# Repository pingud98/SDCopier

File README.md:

# SDCopier
A cheap and simple board to copy SD cards

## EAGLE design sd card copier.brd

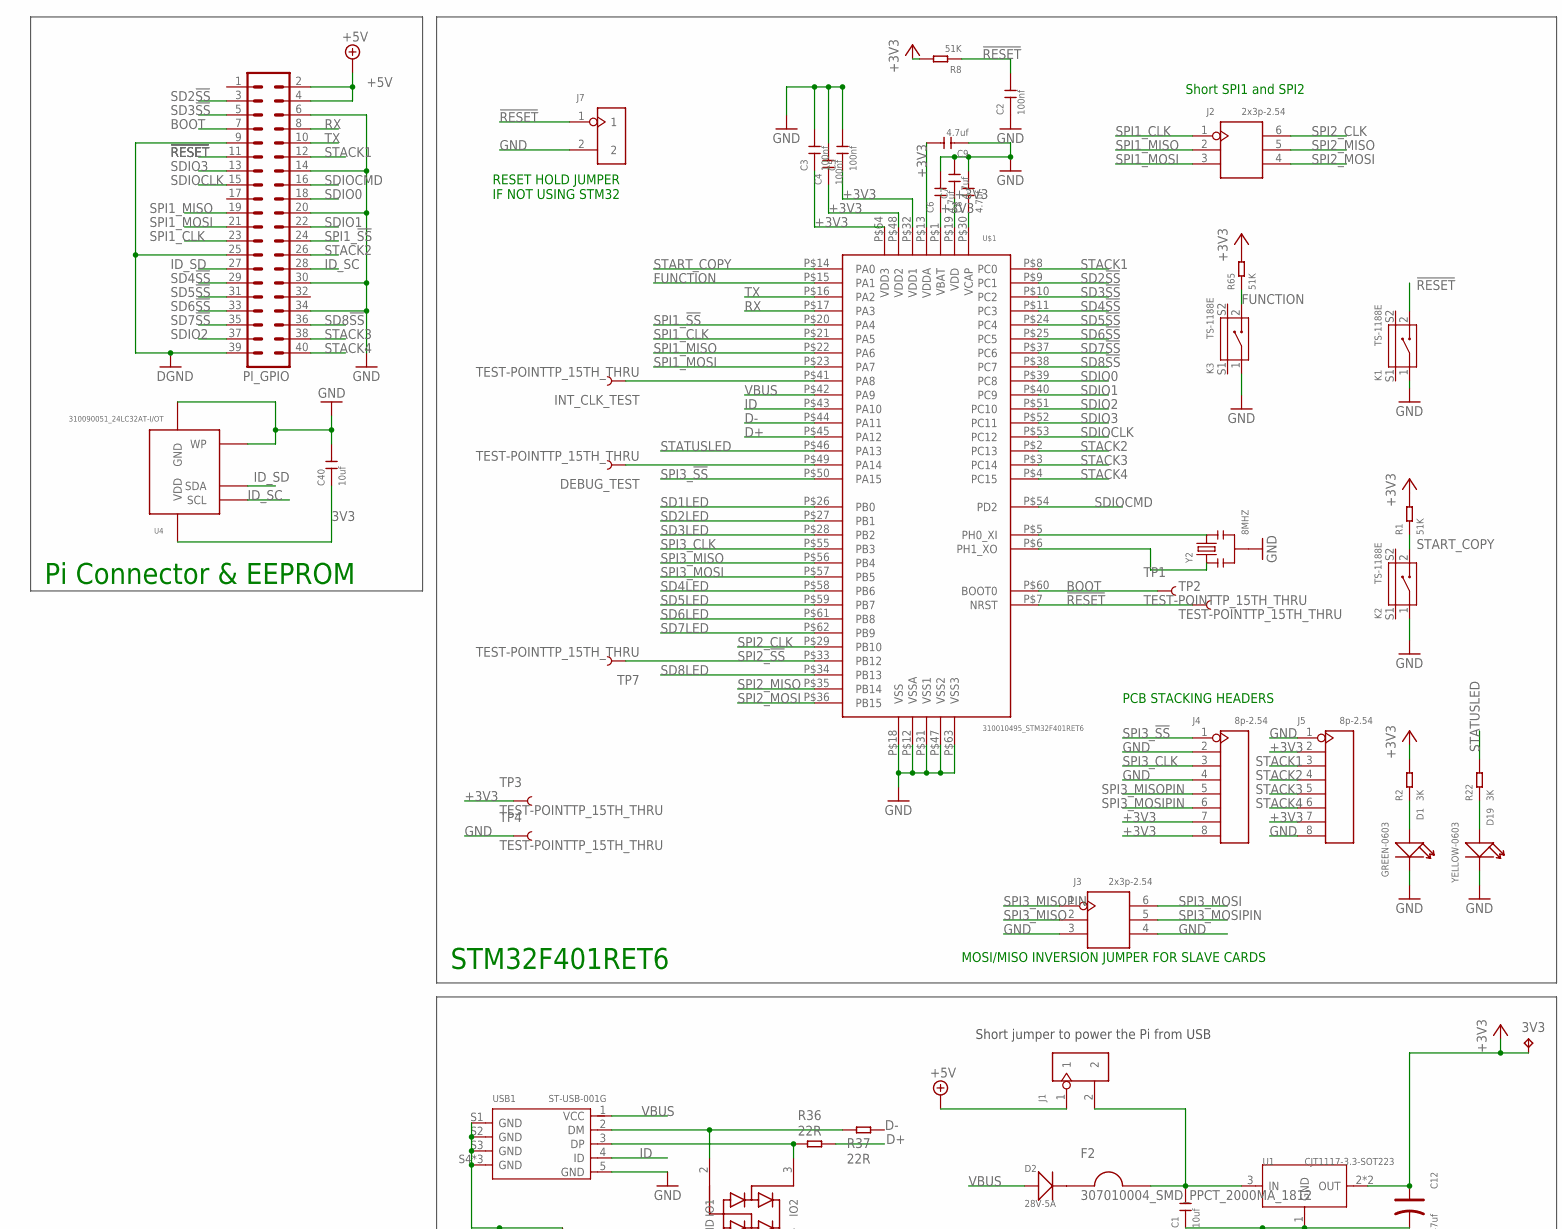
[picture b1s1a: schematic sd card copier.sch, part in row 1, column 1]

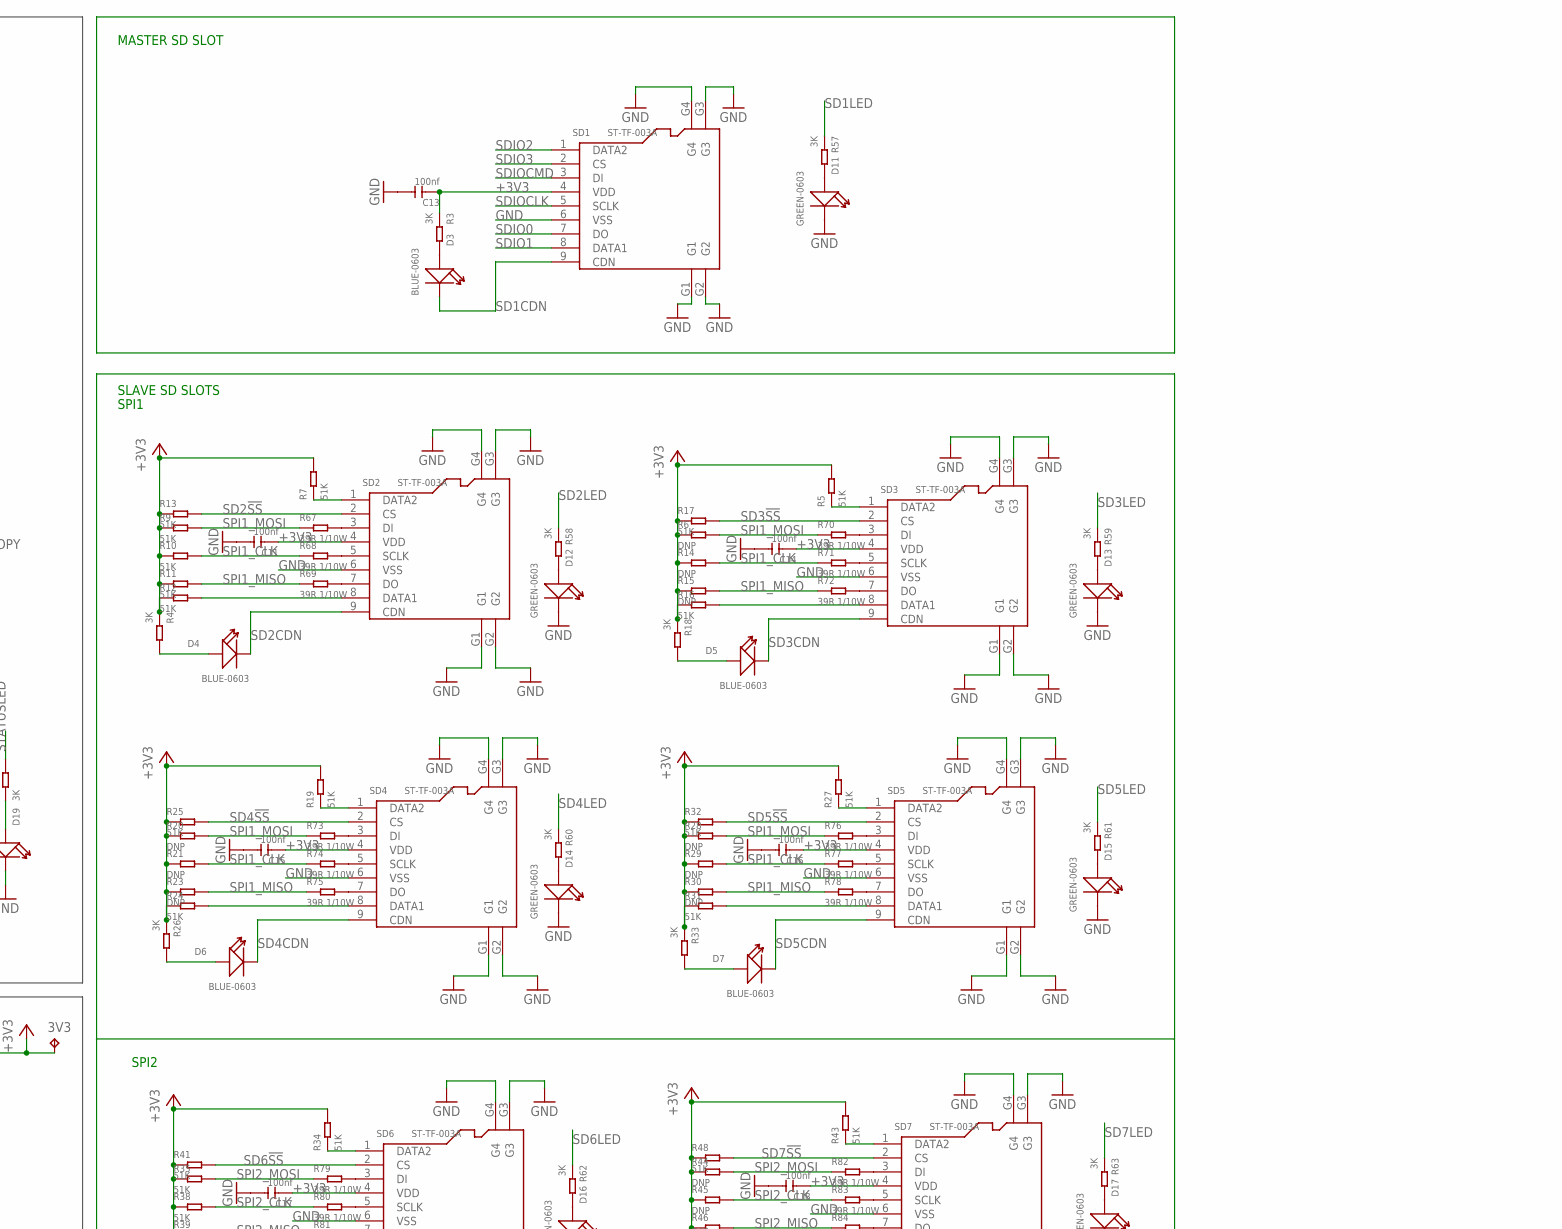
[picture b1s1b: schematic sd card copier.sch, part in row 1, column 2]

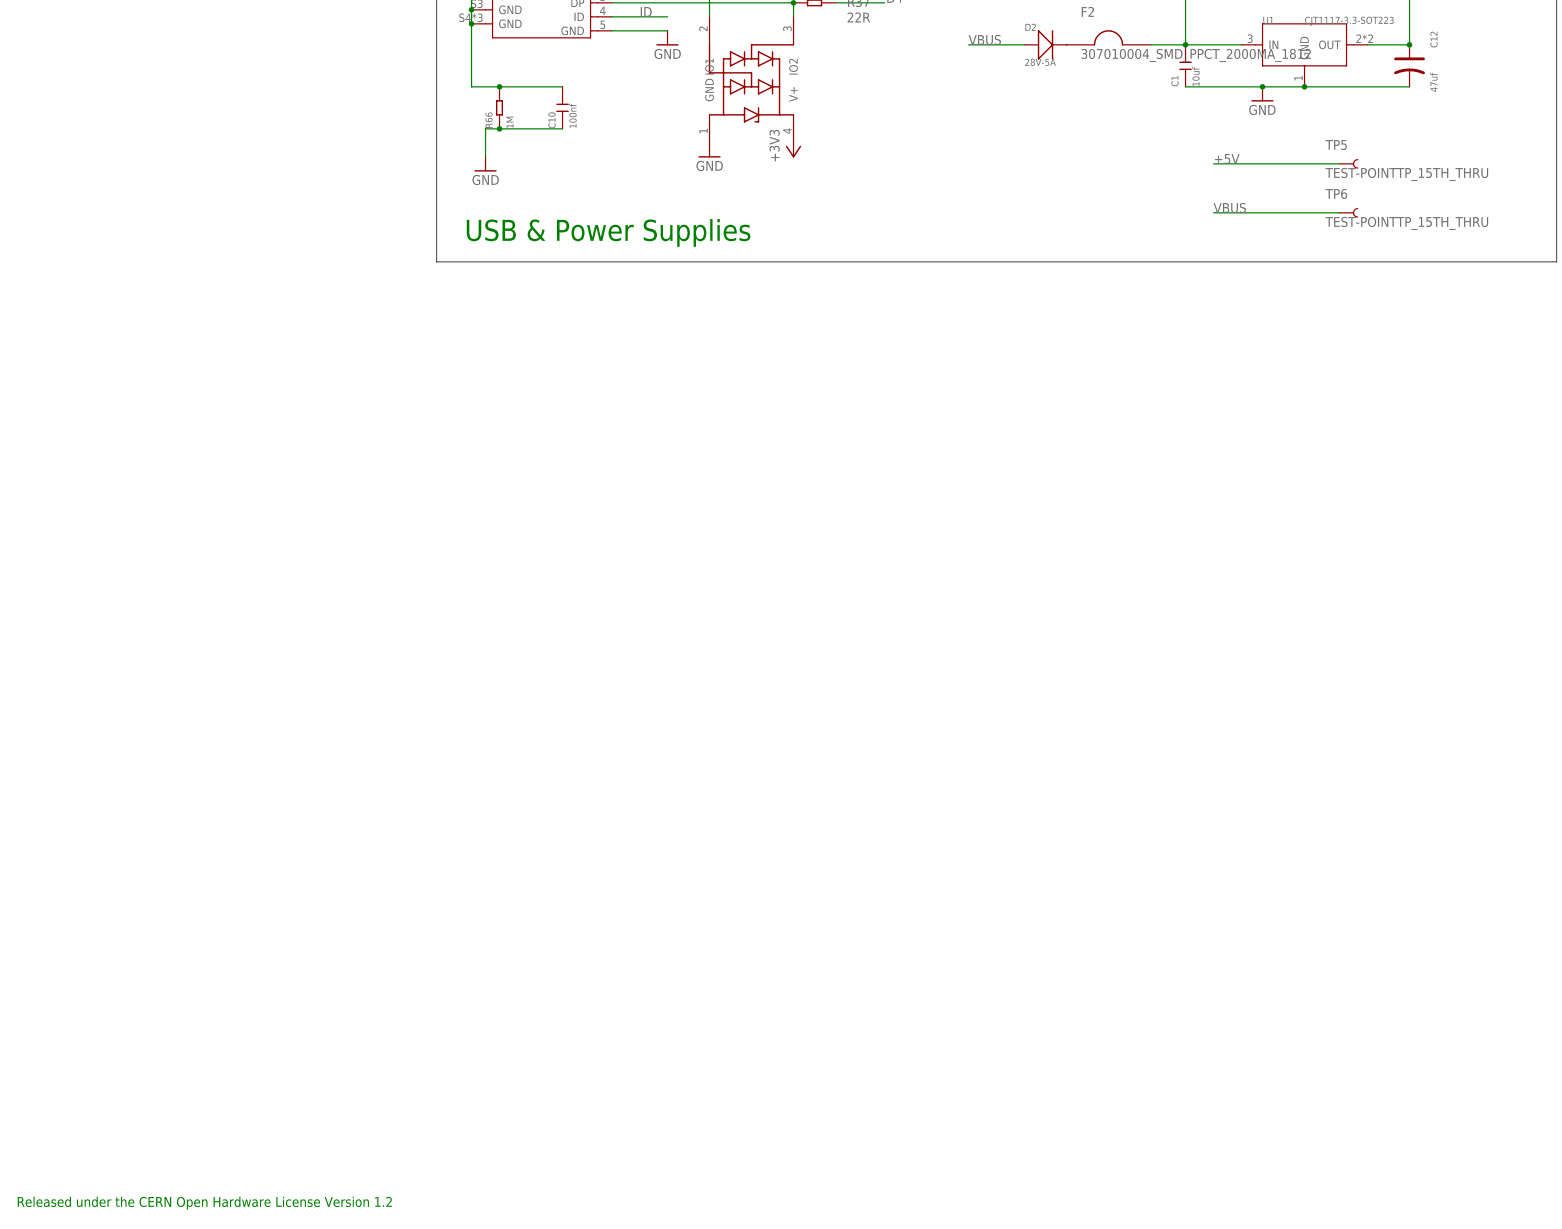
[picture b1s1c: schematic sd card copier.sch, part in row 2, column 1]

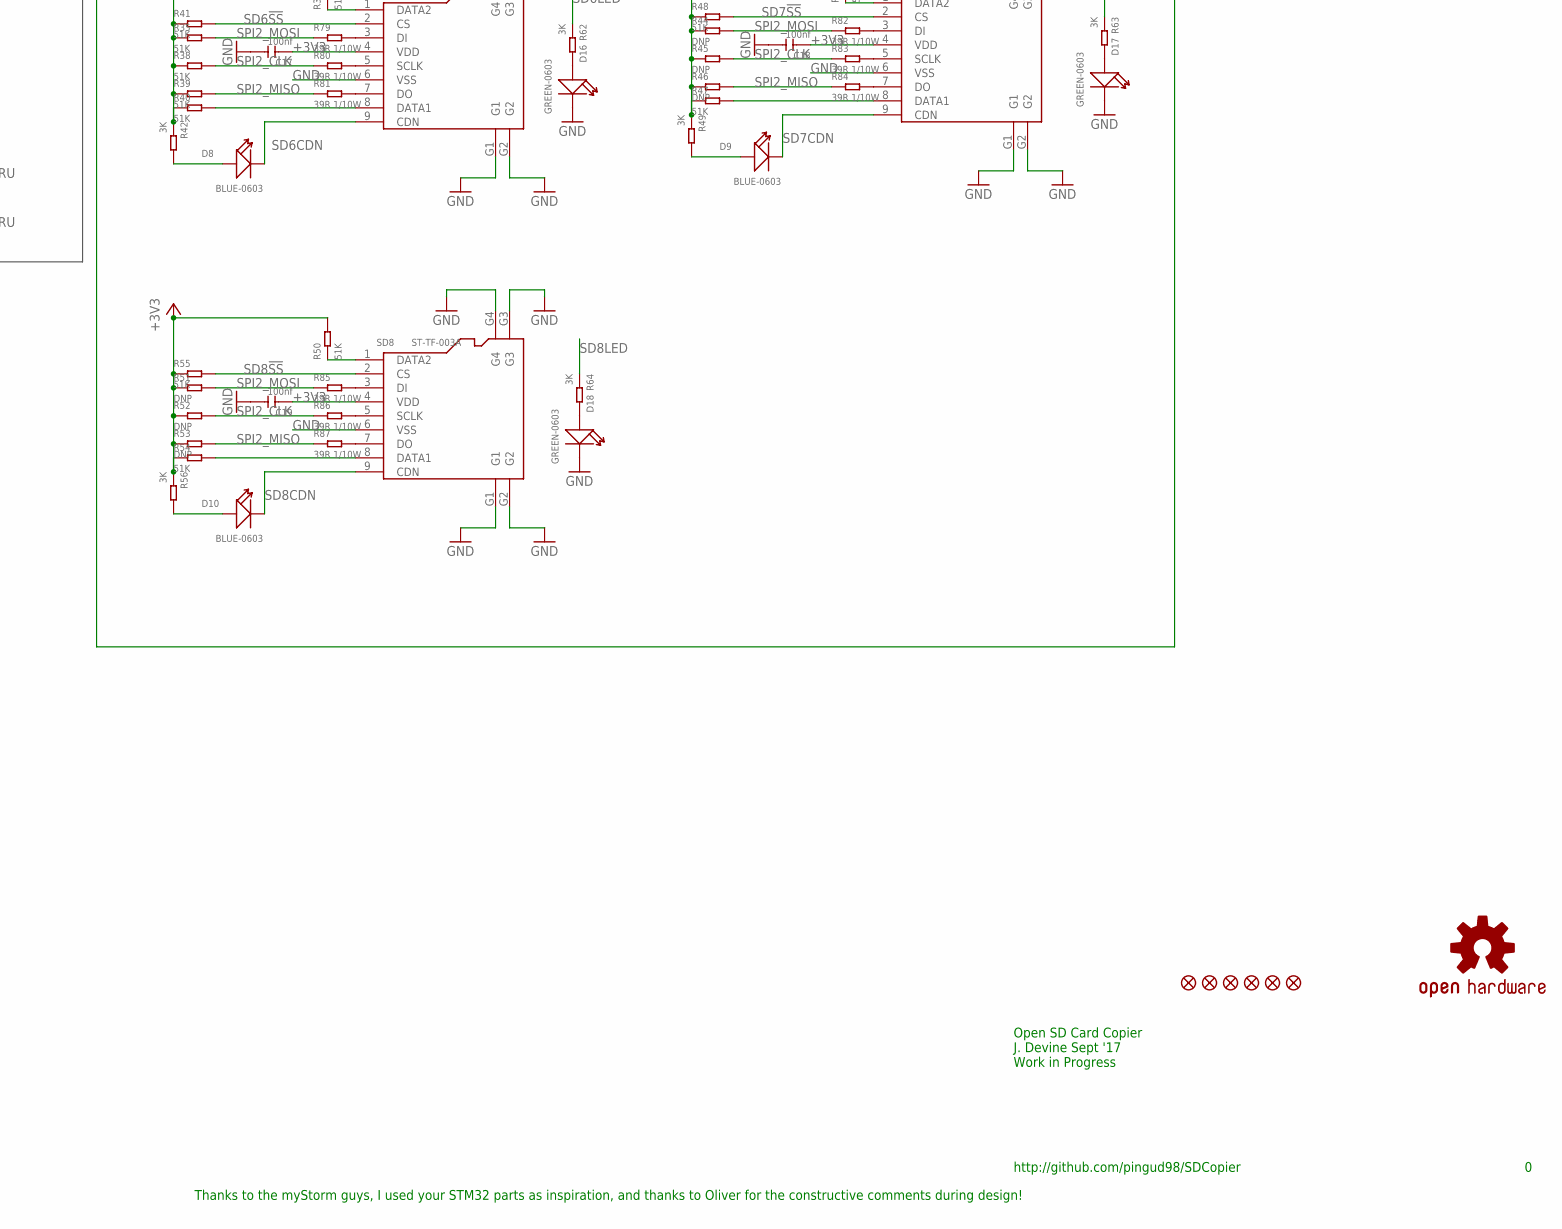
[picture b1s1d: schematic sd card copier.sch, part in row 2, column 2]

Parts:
3V3: TPB1,27; B1,27
C1, C40: 10uf; C0603
C2, C3, C4, C5, C10, C11, C13, C14, C15, C16, C17, C18, C19: 100nf; C0603
C6, C7, C8, C9: 4.7uf; C0603
C12: 47uf; AVX-A
D1, D11, D12, D13, D14, D15, D16, D17, D18: GREEN-0603; LED-0603
D2: 28V-5A; DO-214AA
D3, D4, D5, D6, D7, D8, D9, D10: BLUE-0603; LED-0603
D19: YELLOW-0603; LED-0603
DEBUG_TEST: TEST-POINTTP_15TH_THRU; TP_15TH
ESD1: PRTR5V0U2X; SOT143B
F2: 307010004_SMD_PPCT_2000MA_1812; F1812
FD1, FD2, FD3, FD4, FD5, FD6: FIDUCIAL1X2; FIDUCIAL-1X2
INT_CLK_TEST: TEST-POINTTP_15TH_THRU; TP_15TH
J1, J7: DIP-BLACK-JUMPER; H2-2.54
J2, J3: 2x3p-2.54; H2X3-2.54
J4, J5: 8p-2.54; H8-2.54
K1, K2, K3: TS-1188E; SW4-SMD-7.0X3.5X3.5MM-90D
OSHW: OSHW-LOGOL; OSHW-LOGO-L
PI_GPIO: MA20-2
R1, R5, R7, R8, R9, R10, R11, R12, R13, R16, R17, R19, R24, R25, R27, R31, R32, R34, R35, R38, R39, R40, R41, R43, R47, R48, R50, R54, R55, R65: 51K; R0603
R2, R3, R4, R18, R22, R26, R33, R42, R49, R56, R57, R58, R59, R60, R61, R62, R63, R64: 3K; R0603
R6, R14, R15, R20, R21, R23, R28, R29, R30, R44, R45, R46, R51, R52, R53: DNP; R0603
R36, R37: 22R; R0603
R66: 1M; R0603
R67, R68, R69, R70, R71, R72, R73, R74, R75, R76, R77, R78, R79, R80, R81, R82, R83, R84, R85, R86, R87: 39R 1/10W; R0603
SD1, SD2, SD3, SD4, SD5, SD6, SD7, SD8: ST-TF-003A; MICRO-SD9+4P-SMD-16.1X14.5X1.85MM
TP1, TP2, TP3, TP4, TP5, TP6, TP7: TEST-POINTTP_15TH_THRU; TP_15TH
U1: CJT1117-3.3-SOT223; SOT-223
U4: 310090051_24LC32AT-I/OT; SOT235
U$1: 310010495_STM32F401RET6; LQFP64
USB1: ST-USB-001G; MICRO-USB5+4P-SMD-0.65-B
Y2: 8MHZ; X3-SMD-3.6X1.3X0.8MM

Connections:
3V3: C40.1, U4.4 (VDD)
!RESET: C2.2, J7.1, K1.2, PI_GPIO.11, R8.1, TP2.P$1, U$1.P$7 (NRST)
+3V3: 3V3.TP, C3.1, C4.1, C5.1, C6.1, C7.1, C9.2, C11.1, C12.+, C13.1, C14.1, C15.1, C16.1, C17.1, C18.1, C19.1, ESD1.4 (V+), J4.7, J4.8, J5.2, J5.7, R1.2, R2.2, R3.1, R4.1, R5.2, R6.1, R7.2, R8.2, R9.1, R10.1, R11.1, R12.1, R13.1, R14.1, R15.1, R16.1, R17.1, R18.1, R19.2, R20.1, R21.1, R23.1, R24.1, R25.1, R26.1, R27.2, R28.1, R29.1, R30.1, R31.1, R32.1, R33.1, R34.2, R35.1, R38.1, R39.1, R40.1, R41.1, R42.1, R43.2, R44.1, R45.1, R46.1, R47.1, R48.1, R49.1, R50.2, R51.1, R52.1, R53.1, R54.1, R55.1, R56.1, R65.2, SD1.4 (VDD), SD2.4 (VDD), SD3.4 (VDD), SD4.4 (VDD), SD5.4 (VDD), SD6.4 (VDD), SD7.4 (VDD), SD8.4 (VDD), TP3.P$1, U1.2 (OUT), U1.TER (OUT), U$1.P$1 (VBAT), U$1.P$13 (VDDA), U$1.P$19 (VDD), U$1.P$32 (VDD1), U$1.P$48 (VDD2), U$1.P$64 (VDD3)
+5V: J1.1, PI_GPIO.2, PI_GPIO.4, TP5.P$1
BOOT: PI_GPIO.7, TP1.P$1, U$1.P$60 (BOOT0)
D+: R36.1, U$1.P$45 (PA12)
D-: R37.1, U$1.P$44 (PA11)
FUNCTION: K3.2, R65.1, U$1.P$15 (PA1)
GND: C1.1, C2.1, C3.2, C4.2, C5.2, C6.2, C7.2, C8.2, C9.1, C10.1, C11.2, C12.-, C13.2, C14.2, C15.2, C16.2, C17.2, C18.2, C19.2, C40.2, D1.-, D11.-, D12.-, D13.-, D14.-, D15.-, D16.-, D17.-, D18.-, D19.-, ESD1.1 (GND), J3.3, J3.4, J4.2, J4.4, J5.1, J5.8, J7.2, K1.1, K2.1, K3.1, PI_GPIO.6, PI_GPIO.9, PI_GPIO.14, PI_GPIO.20, PI_GPIO.25, PI_GPIO.30, PI_GPIO.34, PI_GPIO.39, R66.1, SD1.6 (VSS), SD1.G1, SD1.G2, SD1.G3, SD1.G4, SD2.6 (VSS), SD2.G1, SD2.G2, SD2.G3, SD2.G4, SD3.6 (VSS), SD3.G1, SD3.G2, SD3.G3, SD3.G4, SD4.6 (VSS), SD4.G1, SD4.G2, SD4.G3, SD4.G4, SD5.6 (VSS), SD5.G1, SD5.G2, SD5.G3, SD5.G4, SD6.6 (VSS), SD6.G1, SD6.G2, SD6.G3, SD6.G4, SD7.6 (VSS), SD7.G1, SD7.G2, SD7.G3, SD7.G4, SD8.6 (VSS), SD8.G1, SD8.G2, SD8.G3, SD8.G4, TP4.P$1, U1.1 (GND), U4.2 (GND), U4.5 (WP), U$1.P$12 (VSSA), U$1.P$18 (VSS), U$1.P$31 (VSS1), U$1.P$47 (VSS2), U$1.P$63 (VSS3), USB1.5 (GND), Y2.2
ID: U$1.P$43 (PA10), USB1.4 (ID)
ID_SC: PI_GPIO.28, U4.1 (SCL)
ID_SD: PI_GPIO.27, U4.3 (SDA)
unnamed: D1.+, R2.1
unnamed: D2.-, F2.P$1
unnamed: C8.1, U$1.P$30 (VCAP)
unnamed: C10.2, R66.2, USB1.S1 (GND), USB1.S2 (GND), USB1.S3 (GND), USB1.S4 (GND), USB1.S5 (GND), USB1.S6 (GND)
unnamed: ESD1.3 (IO2), R36.2, USB1.3 (DP)
unnamed: ESD1.2 (IO1), R37.2, USB1.2 (DM)
unnamed: U$1.P$5 (PH0_XI), Y2.3
unnamed: C1.2, F2.P$2, J1.2, U1.3 (IN)
unnamed: D4.+, R4.2
unnamed: D3.+, R3.2
unnamed: R16.2, SD3.8 (DATA1)
unnamed: R5.1, SD3.1 (DATA2)
unnamed: D5.+, R18.2
unnamed: R24.2, SD4.8 (DATA1)
unnamed: U$1.P$6 (PH1_XO), Y2.1
unnamed: R12.2, SD2.8 (DATA1)
unnamed: R19.1, SD4.1 (DATA2)
unnamed: R7.1, SD2.1 (DATA2)
unnamed: D6.+, R26.2
unnamed: R31.2, SD5.8 (DATA1)
unnamed: R27.1, SD5.1 (DATA2)
unnamed: D7.+, R33.2
unnamed: R43.1, SD7.1 (DATA2)
unnamed: R34.1, SD6.1 (DATA2)
unnamed: D8.+, R42.2
unnamed: D9.+, R49.2
unnamed: R47.2, SD7.8 (DATA1)
unnamed: R50.1, SD8.1 (DATA2)
unnamed: R40.2, SD6.8 (DATA1)
unnamed: D10.+, R56.2
unnamed: R54.2, SD8.8 (DATA1)
unnamed: D11.+, R57.2
unnamed: D12.+, R58.2
unnamed: D13.+, R59.2
unnamed: D14.+, R60.2
unnamed: D15.+, R61.2
unnamed: D16.+, R62.2
unnamed: D17.+, R63.2
unnamed: D18.+, R64.2
unnamed: D19.+, R22.1
unnamed: R67.2, SD2.3 (DI)
unnamed: R68.2, SD2.5 (SCLK)
unnamed: R69.2, SD2.7 (DO)
unnamed: R70.2, SD3.3 (DI)
unnamed: R71.2, SD3.5 (SCLK)
unnamed: R72.2, SD3.7 (DO)
unnamed: R73.2, SD4.3 (DI)
unnamed: R74.2, SD4.5 (SCLK)
unnamed: R75.2, SD4.7 (DO)
unnamed: R76.2, SD5.3 (DI)
unnamed: R77.2, SD5.5 (SCLK)
unnamed: R78.2, SD5.7 (DO)
unnamed: R79.2, SD6.3 (DI)
unnamed: R80.2, SD6.5 (SCLK)
unnamed: R81.2, SD6.7 (DO)
unnamed: R82.2, SD7.3 (DI)
unnamed: R83.2, SD7.5 (SCLK)
unnamed: R84.2, SD7.7 (DO)
unnamed: R85.2, SD8.3 (DI)
unnamed: R86.2, SD8.5 (SCLK)
unnamed: R87.2, SD8.7 (DO)
unnamed: INT_CLK_TEST.P$1, U$1.P$41 (PA8)
unnamed: DEBUG_TEST.P$1, U$1.P$49 (PA14)
RX: PI_GPIO.8, U$1.P$17 (PA3)
SD1CDN: D3.-, SD1.9 (CDN)
SD1LED: R57.1, U$1.P$26 (PB0)
SD2!SS: PI_GPIO.3, R13.2, SD2.2 (CS), U$1.P$9 (PC1)
SD2CDN: D4.-, SD2.9 (CDN)
SD2LED: R58.1, U$1.P$27 (PB1)
SD3!SS: PI_GPIO.5, R17.2, SD3.2 (CS), U$1.P$10 (PC2)
SD3CDN: D5.-, SD3.9 (CDN)
SD3LED: R59.1, U$1.P$28 (PB2)
SD4!SS: PI_GPIO.29, R25.2, SD4.2 (CS), U$1.P$11 (PC3)
SD4CDN: D6.-, SD4.9 (CDN)
SD4LED: R60.1, U$1.P$58 (PB6)
SD5!SS: PI_GPIO.31, R32.2, SD5.2 (CS), U$1.P$24 (PC4)
SD5CDN: D7.-, SD5.9 (CDN)
SD5LED: R61.1, U$1.P$59 (PB7)
SD6!SS: PI_GPIO.33, R41.2, SD6.2 (CS), U$1.P$25 (PC5)
SD6CDN: D8.-, SD6.9 (CDN)
SD6LED: R62.1, U$1.P$61 (PB8)
SD7!SS: PI_GPIO.35, R48.2, SD7.2 (CS), U$1.P$37 (PC6)
SD7CDN: D9.-, SD7.9 (CDN)
SD7LED: R63.1, U$1.P$62 (PB9)
SD8!SS: PI_GPIO.36, R55.2, SD8.2 (CS), U$1.P$38 (PC7)
SD8CDN: D10.-, SD8.9 (CDN)
SD8LED: R64.1, U$1.P$34 (PB13)
SDIO0: PI_GPIO.18, SD1.7 (DO), U$1.P$39 (PC8)
SDIO1: PI_GPIO.22, SD1.8 (DATA1), U$1.P$40 (PC9)
SDIO2: PI_GPIO.37, SD1.1 (DATA2), U$1.P$51 (PC10)
SDIO3: PI_GPIO.13, SD1.2 (CS), U$1.P$52 (PC11)
SDIOCLK: PI_GPIO.15, SD1.5 (SCLK), U$1.P$53 (PC12)
SDIOCMD: PI_GPIO.16, SD1.3 (DI), U$1.P$54 (PD2)
SPI1_!SS: PI_GPIO.24, U$1.P$20 (PA4)
SPI1_CLK: J2.1, PI_GPIO.23, R10.2, R14.2, R21.2, R29.2, R68.1, R71.1, R74.1, R77.1, U$1.P$21 (PA5)
SPI1_MISO: J2.2, PI_GPIO.19, R11.2, R15.2, R23.2, R30.2, R69.1, R72.1, R75.1, R78.1, U$1.P$22 (PA6)
SPI1_MOSI: J2.3, PI_GPIO.21, R6.2, R9.2, R20.2, R28.2, R67.1, R70.1, R73.1, R76.1, U$1.P$23 (PA7)
SPI2_!SS: TP7.P$1, U$1.P$33 (PB12)
SPI2_CLK: J2.6, R38.2, R45.2, R52.2, R80.1, R83.1, R86.1, U$1.P$29 (PB10)
SPI2_MISO: J2.5, R39.2, R46.2, R53.2, R81.1, R84.1, R87.1, U$1.P$35 (PB14)
SPI2_MOSI: J2.4, R35.2, R44.2, R51.2, R79.1, R82.1, R85.1, U$1.P$36 (PB15)
SPI3_!SS: J4.1, U$1.P$50 (PA15)
SPI3_CLK: J4.3, U$1.P$55 (PB3)
SPI3_MISO: J3.2, U$1.P$56 (PB4)
SPI3_MISOPIN: J3.1, J4.5
SPI3_MOSI: J3.6, U$1.P$57 (PB5)
SPI3_MOSIPIN: J3.5, J4.6
STACK1: J5.3, PI_GPIO.12, U$1.P$8 (PC0)
STACK2: J5.4, PI_GPIO.26, U$1.P$2 (PC13)
STACK3: J5.5, PI_GPIO.38, U$1.P$3 (PC14)
STACK4: J5.6, PI_GPIO.40, U$1.P$4 (PC15)
START_COPY: K2.2, R1.1, U$1.P$14 (PA0)
STATUSLED: R22.2, U$1.P$46 (PA13)
TX: PI_GPIO.10, U$1.P$16 (PA2)
VBUS: D2.+, TP6.P$1, U$1.P$42 (PA9), USB1.1 (VCC)

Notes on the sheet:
Short jumper to power the Pi from USB
Pi Connector & EEPROM
USB & Power Supplies
STM32F401RET6
Short SPI1 and SPI2
MASTER SD SLOT
SLAVE SD SLOTS
Open SD Card Copier J. Devine Sept '17 Work in Progress
http://github.com/pingud98/SDCopier
Thanks to the myStorm guys, I used your STM32 parts as inspiration, and thanks to Oliver for the constructive comments during design!
RESET HOLD JUMPER IF NOT USING STM32
MOSI/MISO INVERSION JUMPER FOR SLAVE CARDS
PCB STACKING HEADERS
SPI1
SPI2
Released under the CERN Open Hardware License Version 1.2

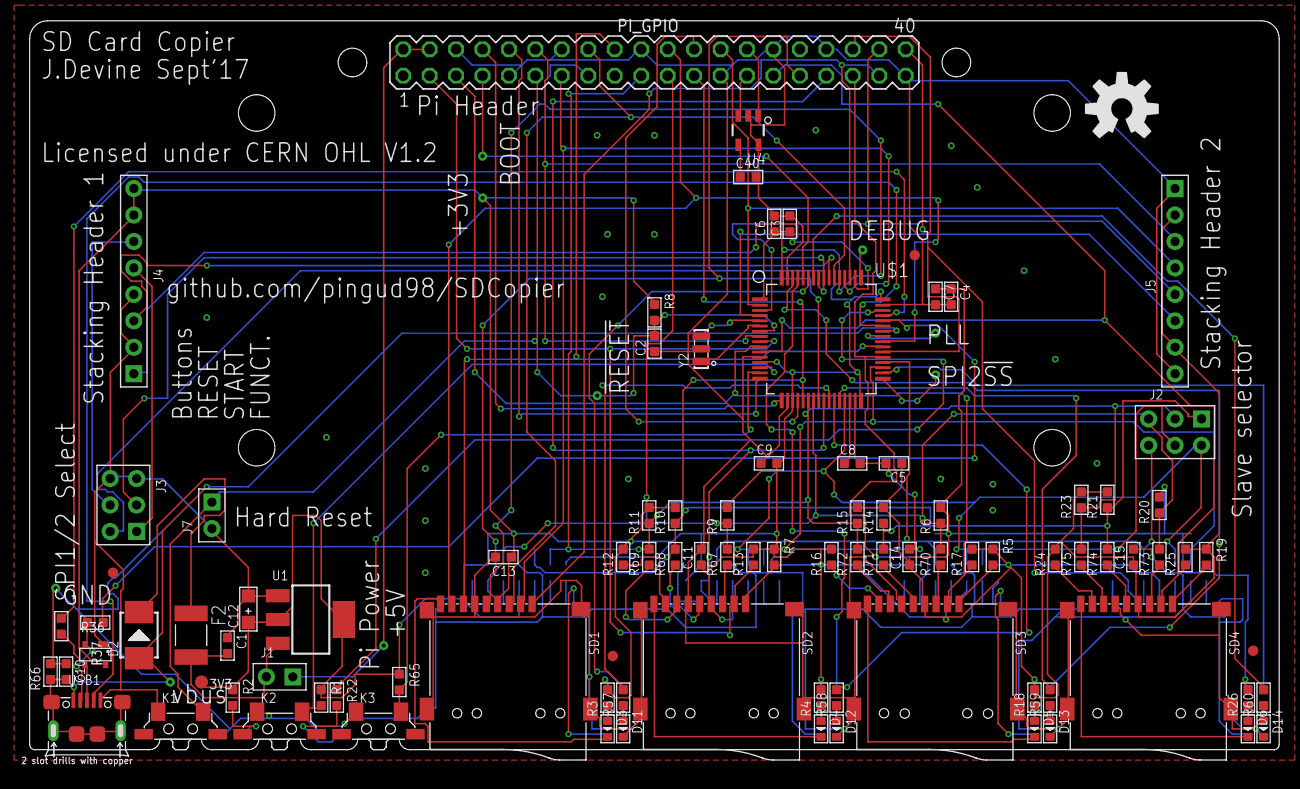
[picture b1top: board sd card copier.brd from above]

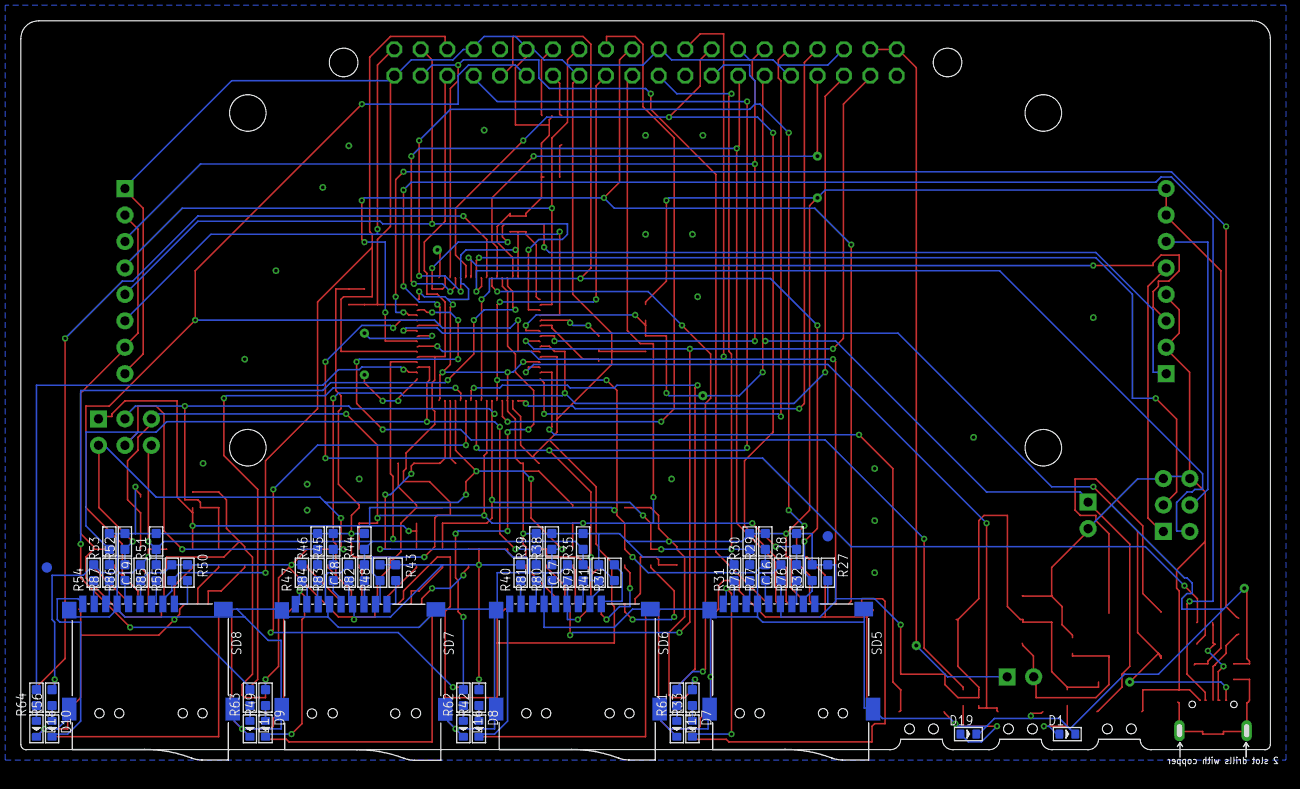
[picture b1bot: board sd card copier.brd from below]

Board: 2 copper layers, 120.0 x 70.7 mm, 168 parts (64 on the bottom side), 127 nets.

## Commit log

2017-09-24 First upload, still working on it
    Check it out, comments welcome!
2017-09-25 Submitted for construction at SEEED
    Time for bed.

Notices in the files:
sd card copier.brd:
Licensed under CERN OHL V1.2
parts and their libraries:
SparkFun-Connectors: Licensing: Creative Commons ShareAlike 4.0 International - https://creativecommons.org/licenses/by-sa/4.0
